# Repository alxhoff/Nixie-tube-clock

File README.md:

# stm32_nixie_clock_firmware
Firmware for a nixie tube clock based on STM32 hal libraries

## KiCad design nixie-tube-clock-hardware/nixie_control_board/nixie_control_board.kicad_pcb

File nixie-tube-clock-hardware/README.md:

# stm32-nixie-tube-clock
Hardware and firmware for a nixie tube clock based around an STM32F0 and DS3231 RTC

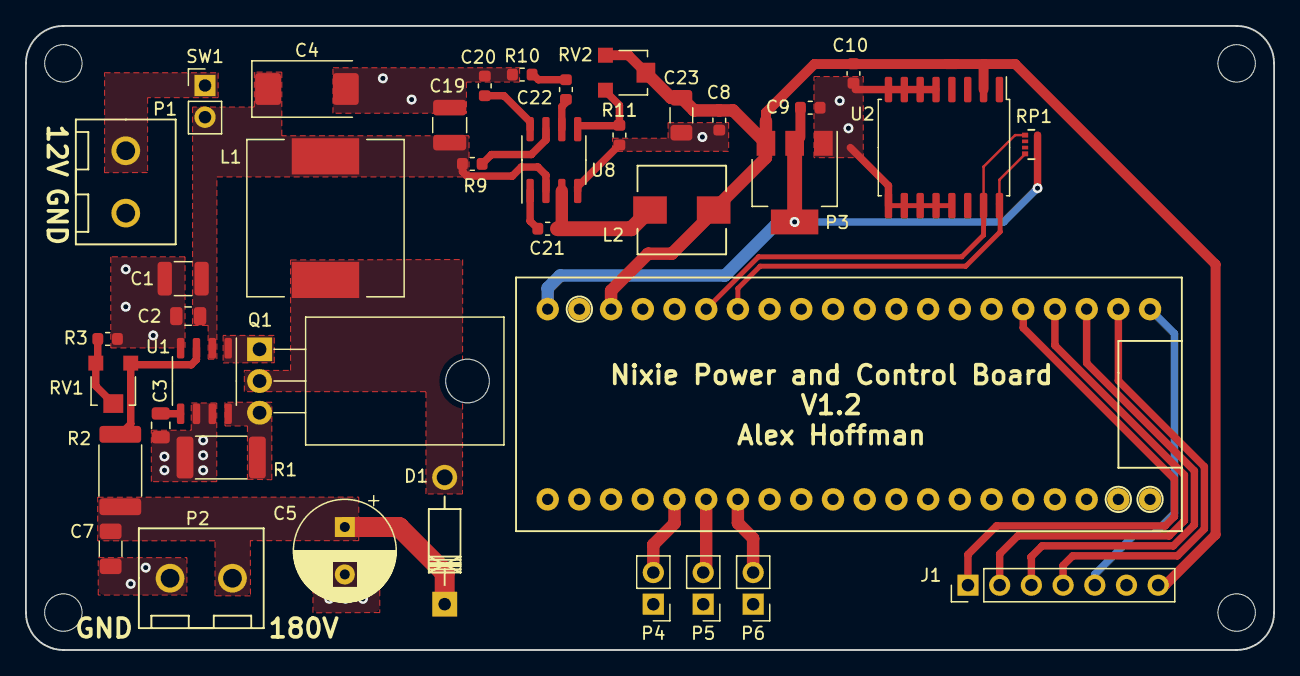
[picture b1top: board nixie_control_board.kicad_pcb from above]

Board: 2 copper layers, 100.0 x 50.0 mm, 39 parts (0 on the bottom side), 29 nets.

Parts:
C1: 10uF, 25V; C_1210_3225Metric
C2, C3: 100nF; C_0805_2012Metric
C4: 100uF, 25V; CP_EIA-7343-15_Kemet-W
C5: 4.7uF/250V; CP_Radial_D8.0mm_P3.80mm
C7: 100nF, 250V; C_1206_3216Metric
C8, C9: 10uF; C_0603_1608Metric
C10: 1uF; C_0603_1608Metric
C19: 10uF/25V; C_1210_3225Metric
C20: 0.1uF; C_0603_1608Metric
C21: 10nF; C_0603_1608Metric
C22: 3.9nF; C_0603_1608Metric
C23: 22uF/6.3V; C_1206_3216Metric
D1: MUR160; Diode_DO-41_SOD81_Horizontal_RM10
J1: Conn_01x07; Pin_Header_Straight_1x07_Pitch2.54mm
L1: 100uH/1.8A; L_12x12mm_H8mm
L2: 10uH; Inductor_Wurth_HCI-7030
MCU1: STM32F103C8T6
P1, P2: CONN_01X02; Power_connectors_5mm
P3: AMS1117; SOT-223
P4, P5, P6: CONN_01X02; PinHeader_1x02_P2.54mm_Vertical
Q1: IRF644; TO-220-3_Horizontal_TabDown
R1: R050; R_2512_6332Metric
R2: 1M5,220V; R_2512_6332Metric
R3: 10K; R_0603_1608Metric
R9: 100k; R_0603_1608Metric
R10: 6.8K; R_0603_1608Metric
R11: 10k; R_0603_1608Metric
RP1: 4K7; R_Array_Convex_4x0402
RV1: 5K; Potentiometer_Trimmer-EVM3E
RV2: 100K(26.1K); Potentiometer_Trimmer-EVM3E
SW1: SW_DIP_x01; PinHeader_1x02_P2.54mm_Vertical
U1: MAX1771; SOP-8_3.9x4.9mm_P1.27mm
U2: DS3231; SOIC-16W_7.5x10.3mm_P1.27mm
U8: MP2307; SOIC-8_3.9x4.9mm_P1.27mm

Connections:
+3V3: C9.1, MCU1.21 (3V3), P3.2 (Vout), P3.4 (Vout), RP1.1 (R1.1), RP1.2 (R2.1), RP1.3 (R3.1), RP1.4 (R4.1)
+5V: C8.1, C10.1, C23.2, J1.7, L2.2, MCU1.23 (5V), P3.3 (Vin), RV2.1, RV2.2, U2.2 (Vcc)
+12P: P1.1, SW1.1
+12V: C1.1, C2.1, C4.1, C19.1, L1.1, R9.2, SW1.2, U1.2 (V+), U8.2 (VIN)
BUTTON_1: MCU1.16 (PA0), P4.2
BUTTON_2: MCU1.15 (PA1), P5.2
BUTTON_3: MCU1.14 (PA2), P6.2
GND: C1.2, C2.2, C3.2, C4.2, C5.2, C7.2, C8.2, C9.2, C10.2, C19.2, C20.1, C23.1, J1.6, MCU1.1 (GND), MCU1.2 (GND), MCU1.22 (GND), P1.2, P2.1, P3.1 (GND/Adj), P4.1, P5.1, P6.1, R1.2, R3.2, R10.1, R11.1, U1.4 (SHDN), U1.6 (AGND), U1.7 (GND), U2.5 (NC), U2.6 (NC), U2.7 (NC), U2.8 (NC), U2.9 (NC), U2.10 (NC), U2.11 (NC), U2.12 (NC), U2.13 (GND), U8.4 (GND)
unnamed: C3.1, U1.5 (REF)
unnamed: C5.1, C7.1, D1.1 (K), P2.2, R2.1
unnamed: C20.2, U8.8 (SS)
unnamed: C21.1, L2.1, U8.3 (SW)
unnamed: C21.2, U8.1 (BST)
unnamed: C22.1, R10.2
unnamed: C22.2, U8.6 (COMP)
unnamed: D1.2 (A), L1.2, Q1.2 (D)
unnamed: Q1.3 (S), R1.1, U1.8 (CS)
unnamed: R2.2, RV1.1, U1.3 (FB)
unnamed: R3.1, RV1.2, RV1.3
unnamed: R9.1, U8.7 (EN)
unnamed: R11.2, RV2.3, U8.5 (FB)
unnamed: Q1.1 (G), U1.1 (EXT)
SCL: MCU1.27 (PB6), RP1.8 (R1.2), U2.16 (SCL)
SDA: MCU1.26 (PB7), RP1.5 (R4.2), U2.15 (SDA)
SHIFT_CLEAR: J1.1, MCU1.36 (PA8)
SHIFT_LATCH_CLOCK: J1.3, MCU1.38 (PB14)
SHIFT_OUT_ENABLE: J1.2, MCU1.37 (PB15)
SHIFT_SERIAL_CLOCK: J1.4, MCU1.39 (PB13)
SHIFT_SER_OUT: J1.5, MCU1.40 (PB12)

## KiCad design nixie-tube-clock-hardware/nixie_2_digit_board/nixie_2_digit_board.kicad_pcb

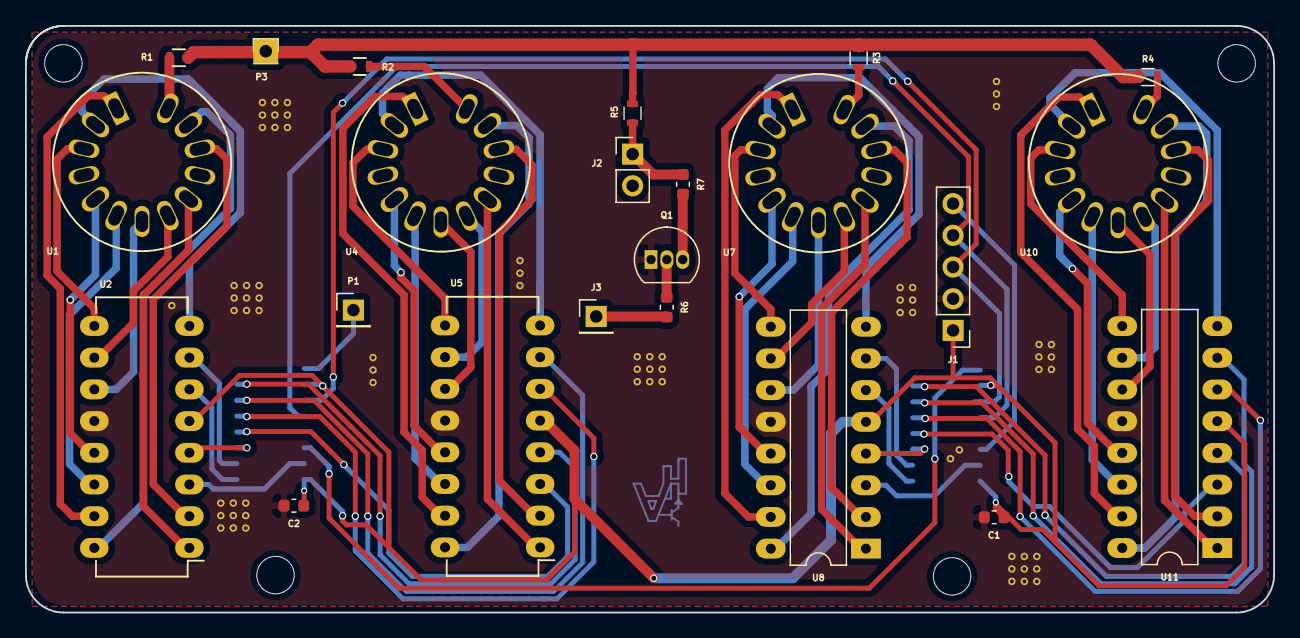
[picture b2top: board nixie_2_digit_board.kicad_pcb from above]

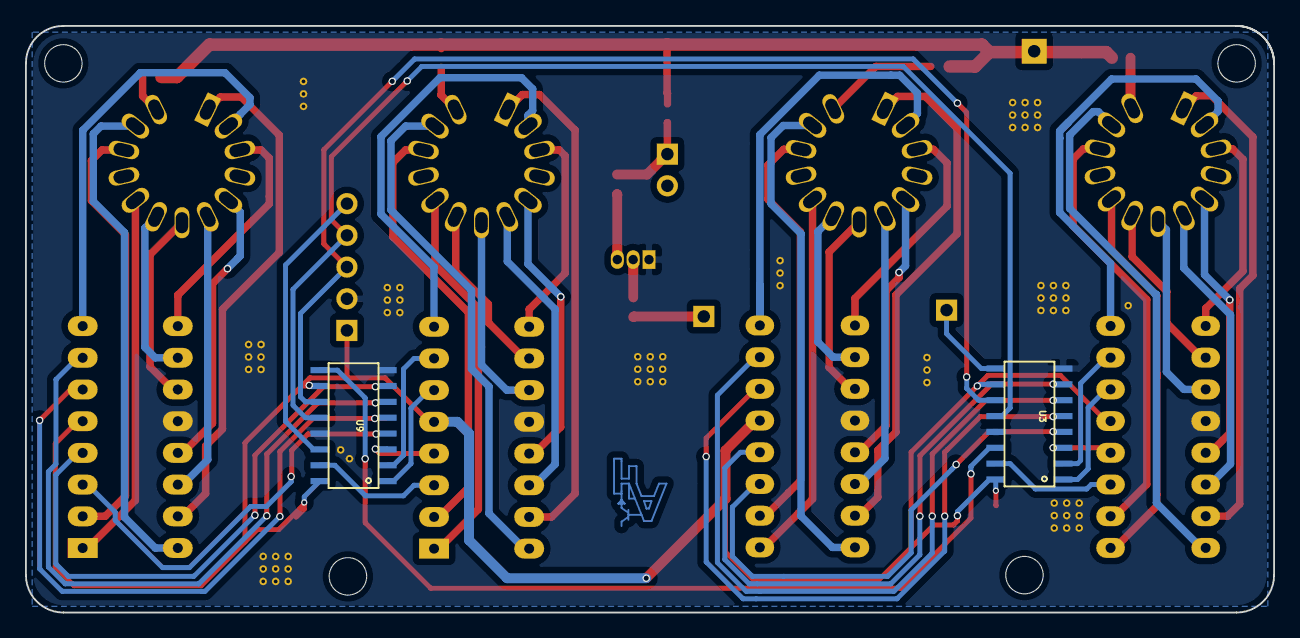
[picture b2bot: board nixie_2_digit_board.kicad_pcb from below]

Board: 2 copper layers, 100.0 x 47.0 mm, 26 parts (3 on the bottom side), 72 nets.

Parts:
C1, C2: 0.1uF; C_0603_1608Metric
J1: Conn_01x05; Pin_Header_Straight_1x05_Pitch2.54mm
J2: Dot Connection; Pin_Header_Straight_1x02_Pitch2.54mm
J3: GPIO in for dot; PinHeader_1x01_P2.54mm_Vertical
P1: CONN_01X01; Pin_Header_Straight_1x01_Pitch2.54mm
P3: CONN_01X01; Pin_Header_Straight_1x01
Q1: MPSA42; TO-92_Inline
R1, R2, R3, R4, R5: 15K; R_0603
R6: 10K; R_0603_1608Metric
R7: 15K; R_0603_1608Metric
U1, U4, U7, U10: 570Nixie; Nixie-570M-573M
U2, U5, U8, U11: SN74141-BCD-DEC-DECODE; DIP-16_W7.62mm_LongPads
U3, U9: SN43HC595; SOP16L
U6: Logo

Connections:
180V: P3.1, R1.1, R2.1, R3.1, R4.1, R5.2
+5V: C1.1, C2.1, J1.1, U2.5, U3.10, U3.16, U5.5, U8.5, U9.10, U9.16, U11.5
DOT_CTRL: J3.1, R6.2
GND: C1.2, C2.2, J1.2, Q1.1, U2.12, U3.8, U3.13, U5.12, U8.12, U9.8, U9.13, U11.12
unnamed: J2.1, R5.1, R7.1
unnamed: P1.1, U3.9
unnamed: Q1.2, R6.1
unnamed: Q1.3, R7.2
unnamed: R1.2, U1.13
unnamed: R2.2, U4.13
unnamed: R3.2, U7.13
unnamed: R4.2, U10.13
unnamed: U1.1, U2.15
unnamed: U1.2, U2.8
unnamed: U1.3, U2.9
unnamed: U1.5, U2.13
unnamed: U1.6, U2.14
unnamed: U1.7, U2.11
unnamed: U1.8, U2.10
unnamed: U1.9, U2.1
unnamed: U1.11, U2.2
unnamed: U1.12, U2.16
unnamed: U2.3, U3.15
unnamed: U2.4, U3.3
unnamed: U2.6, U3.1
unnamed: U2.7, U3.2
unnamed: U3.4, U5.3
unnamed: U3.5, U5.6
unnamed: U3.6, U5.7
unnamed: U3.7, U5.4
unnamed: U4.1, U5.15
unnamed: U4.2, U5.8
unnamed: U4.3, U5.9
unnamed: U4.5, U5.13
unnamed: U4.6, U5.14
unnamed: U4.7, U5.11
unnamed: U4.8, U5.10
unnamed: U4.9, U5.1
unnamed: U4.11, U5.2
unnamed: U4.12, U5.16
unnamed: U7.1, U8.15
unnamed: U7.2, U8.8
unnamed: U7.3, U8.9
unnamed: U7.5, U8.13
unnamed: U7.6, U8.14
unnamed: U7.7, U8.11
unnamed: U7.8, U8.10
unnamed: U7.9, U8.1
unnamed: U7.11, U8.2
unnamed: U7.12, U8.16
unnamed: U8.3, U9.15
unnamed: U8.4, U9.3
unnamed: U8.6, U9.1
unnamed: U8.7, U9.2
unnamed: U10.1, U11.15
unnamed: U10.2, U11.8
unnamed: U10.3, U11.9
unnamed: U10.5, U11.13
unnamed: U10.6, U11.14
unnamed: U10.7, U11.11
unnamed: U10.8, U11.10
unnamed: U10.9, U11.1
unnamed: U10.11, U11.2
unnamed: U10.12, U11.16
unnamed: U9.4, U11.3
unnamed: U9.7, U11.4
unnamed: U9.5, U11.6
unnamed: U9.6, U11.7
SHIFT_LATCH_CLOCK: J1.4, U3.12, U9.12
SHIFT_OUT: U3.14, U9.9
SHIFT_SERIAL_CLOCK: J1.3, U3.11, U9.11
SHIFT_SER_DATA: J1.5, U9.14

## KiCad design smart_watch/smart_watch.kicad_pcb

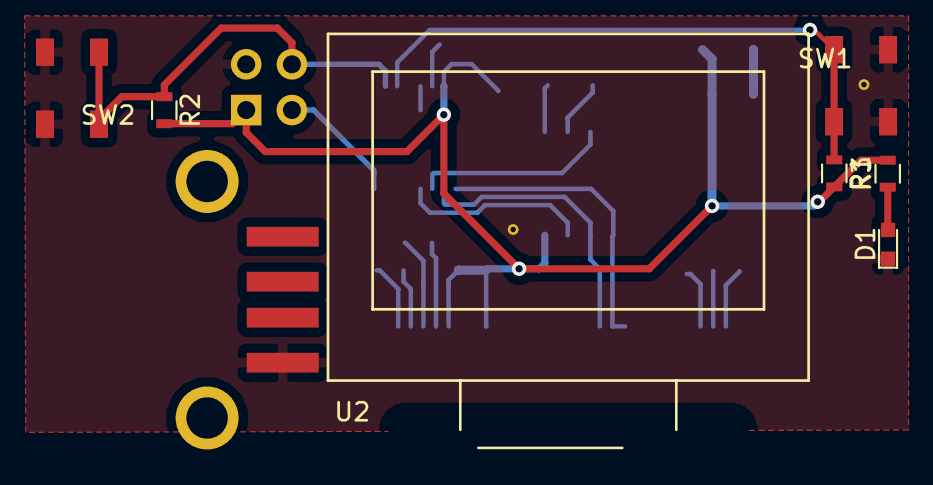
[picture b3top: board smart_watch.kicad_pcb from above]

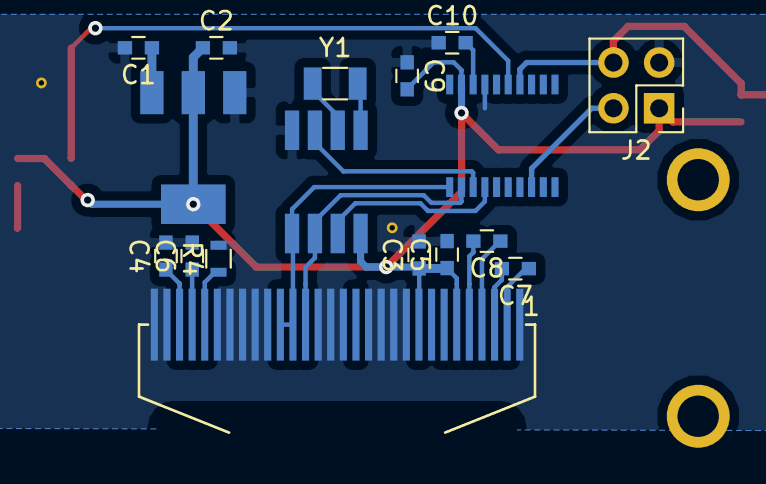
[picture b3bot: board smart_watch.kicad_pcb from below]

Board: 2 copper layers, 24 parts (16 on the bottom side), 21 nets.

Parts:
C1, C2, C3, C4, C5, C6, C7, C8, C10: 1uF; C_0603
C9: 0.1uF; C_0603
D1: LED; LED_0603
J1: USB_A; USB-A-SMT-8231
J2: Conn_01x04; Pin_Header_Straight_2x02_Pitch2.54mm
P1: AMS1117; SOT-223
R1, R2, R3: 1K; R_0603
R4: 1M; R_0603
SW1, SW2: SW_Push; 4_4_1.5_button
U1: DS1337; SO-8
U2: SSD1306-OLED; SSD1306-096-INCH-OLED
U3: STM8S103F3; TSSOP20
Y1: Crystal; Crystal_SMD_3215-2pin_3.2x1.5mm

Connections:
3V3: C2.1, C3.1, C5.1, C9.2, J2.1, P1.2, R1.2, R2.2, R3.2, U1.8, U2.6, U2.9, U3.9
/BAT+: C1.1, P1.3
/SWIM: J2.2, U3.18
GND: C1.2, C2.2, C3.2, C4.2, C5.2, C6.2, C9.1, C10.1, D1.1, J1.4, J2.3, P1.1, R4.2, SW1.2, SW2.2, U1.4, U2.1, U2.8, U2.10, U2.11, U2.12, U2.13, U2.15, U2.16, U2.17, U2.21, U2.22, U2.23, U2.24, U2.25, U2.29, U2.30, U3.7
INTA: U1.3, U3.13
INTB: U1.7, U3.14
unnamed: C4.1, U2.28
unnamed: C6.1, U2.27
unnamed: C7.1, U2.2
unnamed: C7.2, U2.3
unnamed: C8.1, U2.4
unnamed: C8.2, U2.5
unnamed: C10.2, U3.8
unnamed: D1.2, R3.1
unnamed: R4.1, U2.26
unnamed: U1.1, Y1.1
unnamed: U1.2, Y1.2
RESET: J2.4, R2.1, SW2.1, U3.4
SCL: U1.6, U2.18, U3.12
SDA: U1.5, U2.19, U2.20, U3.11
TEST_BTN: R1.1, SW1.1, U3.5

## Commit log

2017-09-13 initial copy across from old repo, needs adapting to purpose
2017-09-16 STM32F4 cube frame work ready for porting from past project
2017-09-16 GPIO and I2C configs
2017-09-17 files copied over from previous project, builds
2017-09-17 git ignore fixed
2017-10-06 old project removed
2017-10-06 basic nixie array code added, needs testing
2017-10-09 stm32f1 project
2017-10-25 CUBE config matched pcb
2017-10-27 shift enable and clear pinouts added
2017-10-27 nixie_clock project builds
2017-10-27 nixie_clock project initial port finished
2017-10-28 zzzzz redone project for nucleoF103RB with propper debug config
2017-10-28 object orientated stuff added
2017-10-29 buttons added and mapped to three button config
2017-10-29 ssd1306 lib updates to accomodate for clear w/wo update
2017-10-29 moved project to non-rtos project, buttons are getting debounced input
2017-10-29 ds3231 self set working
2017-10-29 ds3231 self get working
2017-10-29 draw time ported to use new LCD
2017-10-29 fill time draws
2017-10-30 draws alarm1
2017-10-31 blinking set stuff rewritten, not tested
2017-10-31 set blinking working again
2017-10-31 cycling through non-setting states works
2017-10-31 setting lines working
2017-10-31 can change setting target in time
2017-10-31 draw time and allarm updated
2017-11-02 all setting dashes being drawn, just need them to flash now
2017-11-02 time can be incremented during setting
2017-11-02 middle button jumps from disp to set for each function
2017-11-05 Nixie output compiles
2017-11-05 shift register added
2017-11-29 added rtc->nixie function
2017-11-29 tidy
2018-07-13 prototype shift working
2018-07-14 prototype displaying seconds
2018-07-23 blue pill test code started
2019-01-29 consolidated
2019-02-01 Restarting
2019-02-02 Debug files refreshed
2019-02-02 Let the hacking begin :)
2019-02-02 removed a lot of unnecessary code from RTC_dev
2019-02-02 RTC dev write alarm reduced
2019-02-02 SSD1306 and screen APIs copied across
2019-02-02 Nixie code cut down
2019-02-02 Gets added to RTC dev
2019-02-02 States code imported
2019-02-02 State functions added
2019-02-03 Weekday, date and time drawing to screen
2019-02-03 Alarm printing added, needs testing
2019-02-03 Alarm set fixed
2019-02-03 Alarm 2 printing
2019-02-03 24 hour time converted to 12 hour time if 12 hour format is specified
2019-02-03 Updated shift register code imported
2019-02-03 Clean up
2019-02-03 nixies working
2019-02-04 Hardware updates, bluepill projects added
2019-02-05 Control board updated to encorporate 5v step down and 3.3v reg
2019-02-06 Firmware migrated to newer stm version
2019-02-06 Button interrupt configs and callback added
2019-02-06 Fixed double interrupt firing
2019-02-07 Control board updated to be skinnier and ditch decondary through hole connections
2019-02-09 Button debounce code added
2019-02-09 Time set states and functions added
2019-02-09 Alarm set states and draw functions done
2019-02-09 Basic state transition IO working for first state
2019-02-14 Time set states buttons handled for iterating through set items
2019-02-16 Setting individual time attribute functions added to DS3231
2019-02-16 States handling
2019-02-16 Shifting between big states fixed
2019-02-19 Fixed screen crashing bug
2019-02-19 PCB Identifiers corrected
2019-02-28 updates from mech keyboard
2019-03-02 Screen fixed to abstract FB from screen driver
2019-03-02 fixed shift code, turns out c1 on my nucleo is toast
2019-03-02 Nixie tube output fixed
2019-03-02 Nixie tube output properly fixed
2019-03-03 Modified to output time to 2 shift a 4 nixie
2019-03-05 Screen deffs and nixie states added
2019-03-05 Debounce increased
2019-03-06 Moved time update back outside of ifdef
2019-03-06 Transistor switch added to dot on nixie board
2020-03-31 control board gerber
2020-03-31 nixie board gerber
2020-04-18 Large clean up of old code, reworked state machine
2020-04-18 Formatting
2020-04-18 Rough code added for outputting nixie
2020-04-20 Updated 180V boost supply and updated gitignore
2020-04-25 Clean up and minor fixes
2020-04-25 Added empty bluepill project and moved RT clock battery holder
2020-04-25 Bluepill files added and building, main not reconstructed
2020-04-25 Added tim3 to bluepill project
2020-04-25 Added main code
2020-04-25 Button testing task added
2020-04-26 Added pullups to I2C1
2020-04-27 I2C Working on bluepill
2022-05-29 Some hardware changes
2022-05-30 First fixup after looking at this after 2 years
2022-05-30 V1.2 Control board
2022-06-05 Updated after a few years, not tested working
